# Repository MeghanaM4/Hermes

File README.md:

# Hermes
make a PCB with an on-board sensor to transmit data via I2C, get the money to build it

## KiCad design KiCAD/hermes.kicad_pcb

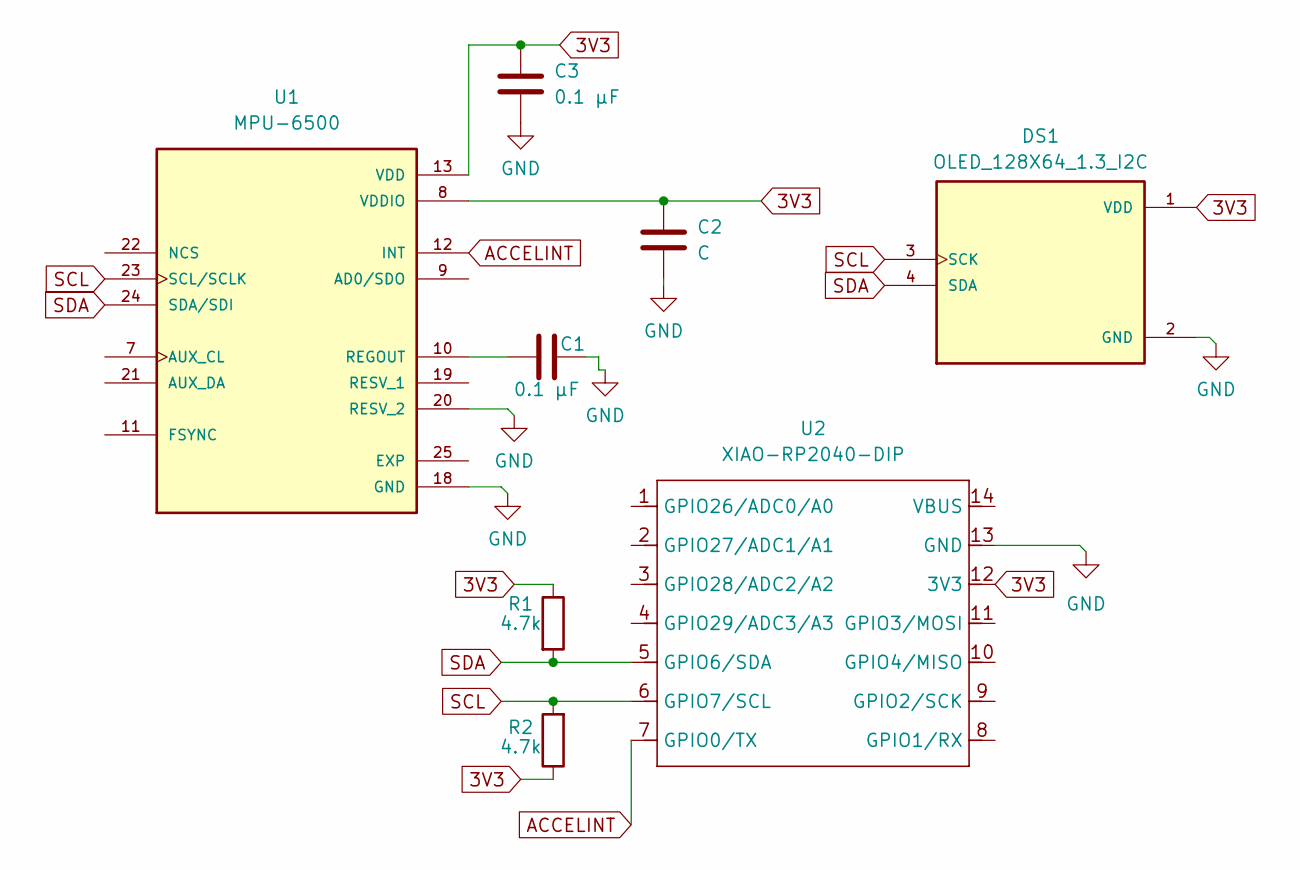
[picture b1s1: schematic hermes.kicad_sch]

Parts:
C1, C3: 0.1 µF; C_1206_3216Metric
C2: C; C_1206_3216Metric
DS1: OLED_128X64_1.3_I2C; 128x64OLED; PARTREV NA
R1, R2: 4.7k; R_Axial_DIN0204_L3.6mm_D1.6mm_P5.08mm_Horizontal
U1: MPU-6500; QFN40P300X300X95-25N; PARTREV 1.3
U2: XIAO-RP2040-DIP

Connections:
3V3: C2.1, C3.1, DS1.1 (VDD), R1.1, R2.1, U1.8 (VDDIO), U1.13 (VDD), U2.12 (3V3)
ACCELINT: U1.12 (INT), U2.7 (GPIO0/TX)
GND: C1.2, C2.2, C3.2, DS1.2 (GND), U1.18 (GND), U1.20 (RESV_2), U2.13 (GND)
unnamed: C1.1, U1.10 (REGOUT)
SCL: DS1.3 (SCK), R2.2, U1.23 (SCL/SCLK), U2.6 (GPIO7/SCL)
SDA: DS1.4 (SDA), R1.2, U1.24 (SDA/SDI), U2.5 (GPIO6/SDA)

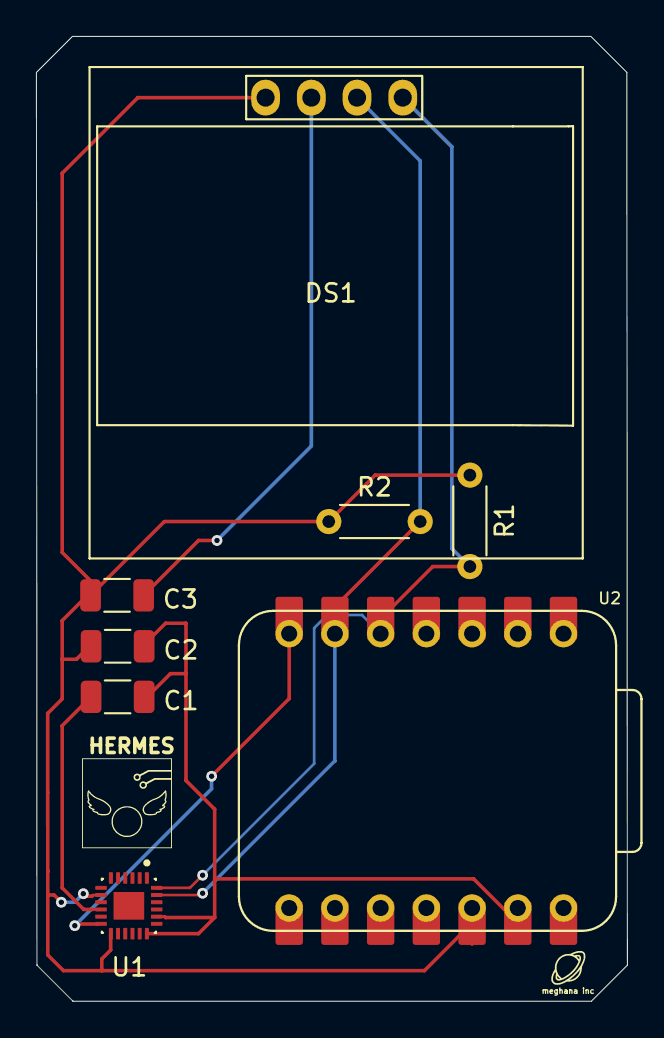
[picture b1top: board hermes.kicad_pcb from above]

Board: 2 copper layers, 32.8 x 53.6 mm, 8 parts (0 on the bottom side), 6 nets.

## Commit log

2025-07-11 buncha stuff
2025-07-13 path + stuff
2025-07-16 step 2 + 3.2
2025-07-17 step 3 + 4
2025-07-18 firmware
2025-07-21 firmware :bangbang: :bangbang:
2025-07-21 Create CNAME
2025-07-21 imgs
2025-07-21 bg again
2025-07-21 crop render
2025-07-22 making firgmware betber
2025-07-22 render
2025-07-22 don't remember
2025-07-22 end date
2025-07-23 help and channel name
2025-07-23 help button formatting + philosophy
2025-07-24 hour typo
2025-07-24 my bad gang
2025-07-24 hour req on popup
2025-10-27 fixed pullups
2025-10-27 PCB update
2025-12-10 fix link
2026-02-04 fixing the wreckage after cdn broke
2026-02-05 no more cdn
2026-02-05 dude I don't even wanna talk about it
2026-02-05 fix render img
2026-04-06 wrong file extension
